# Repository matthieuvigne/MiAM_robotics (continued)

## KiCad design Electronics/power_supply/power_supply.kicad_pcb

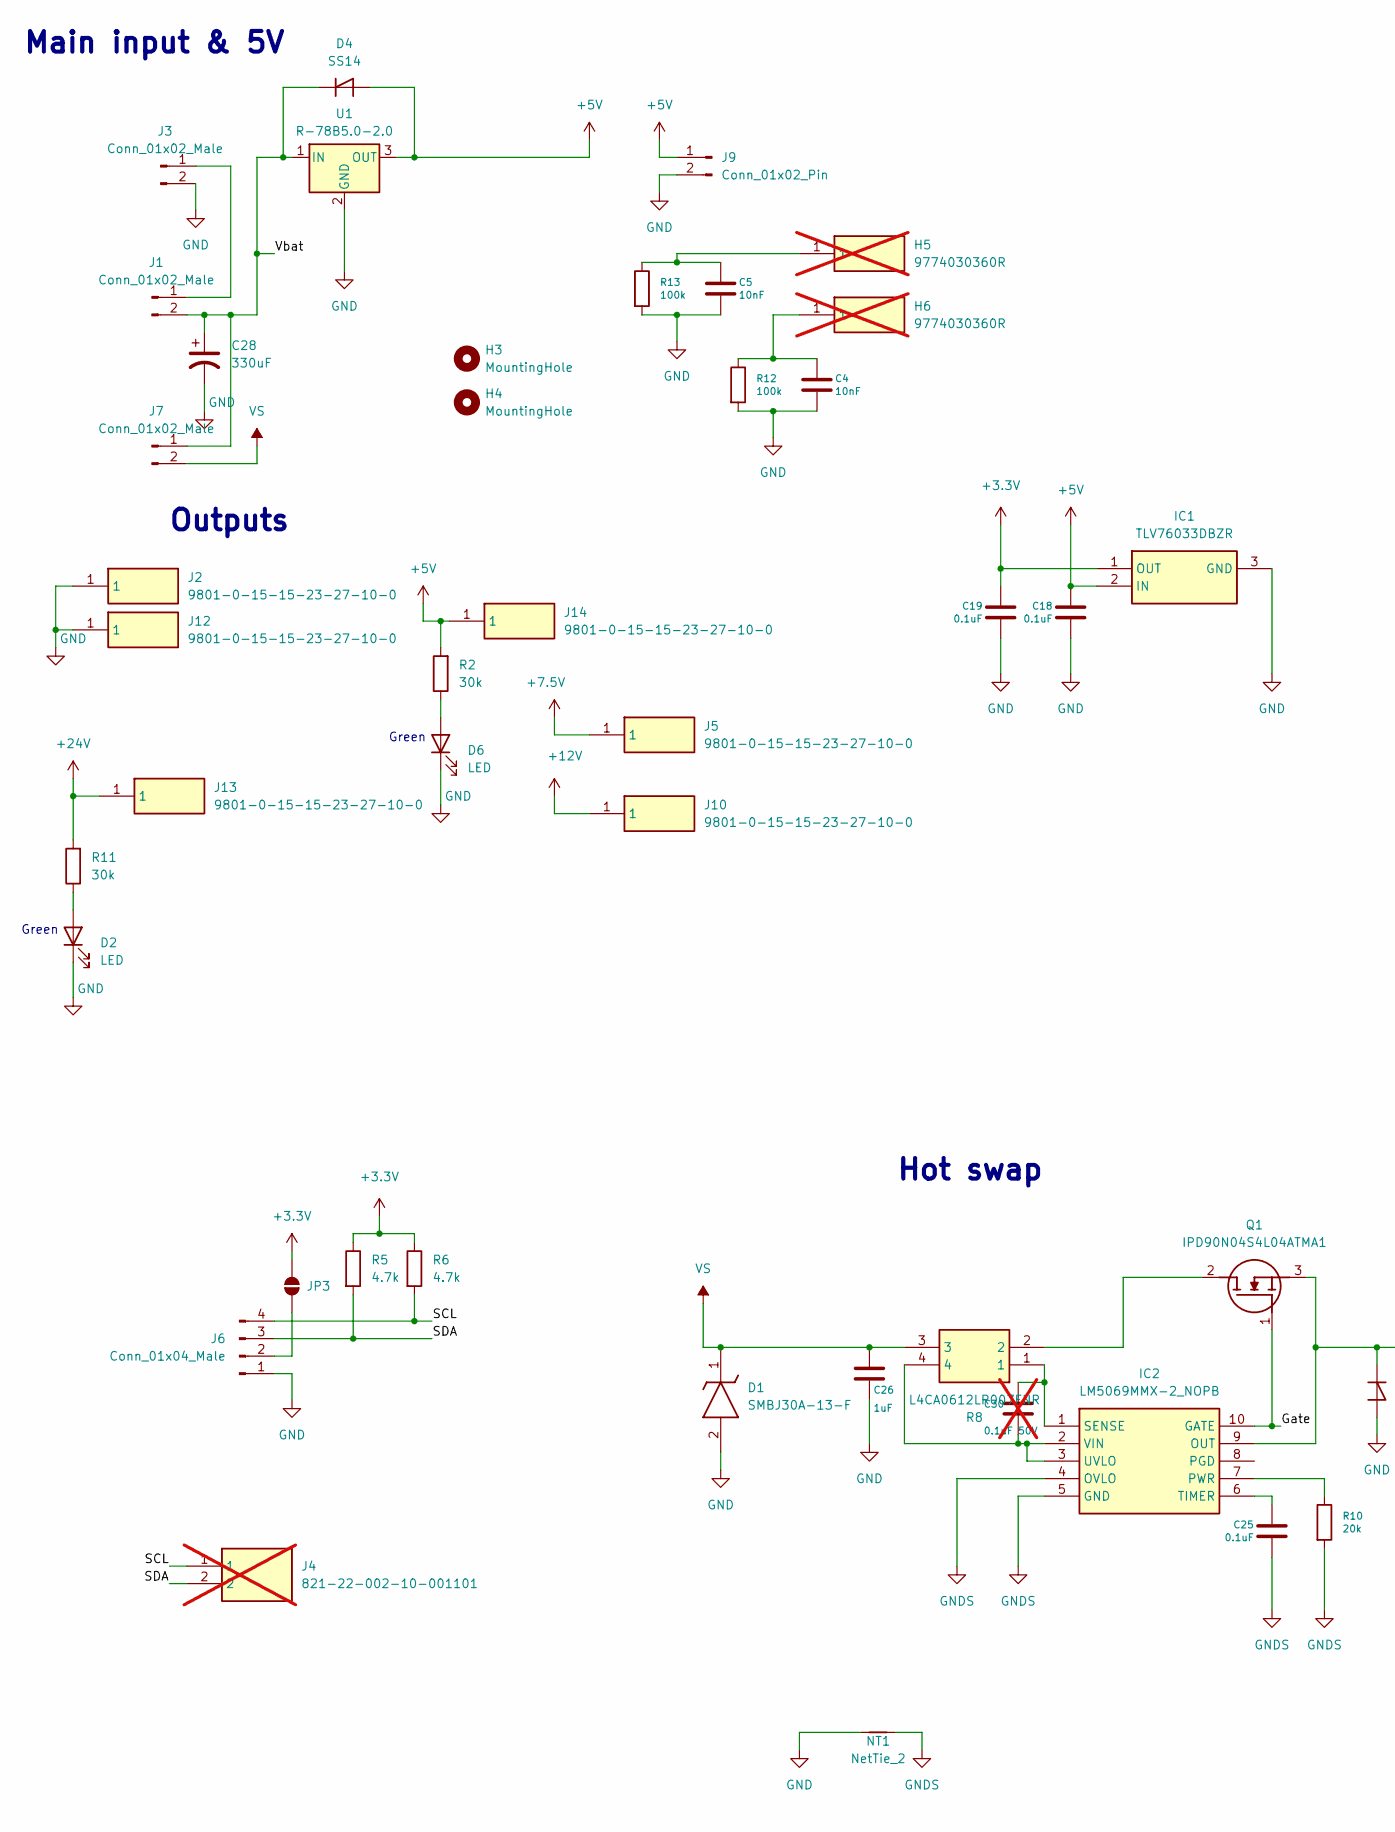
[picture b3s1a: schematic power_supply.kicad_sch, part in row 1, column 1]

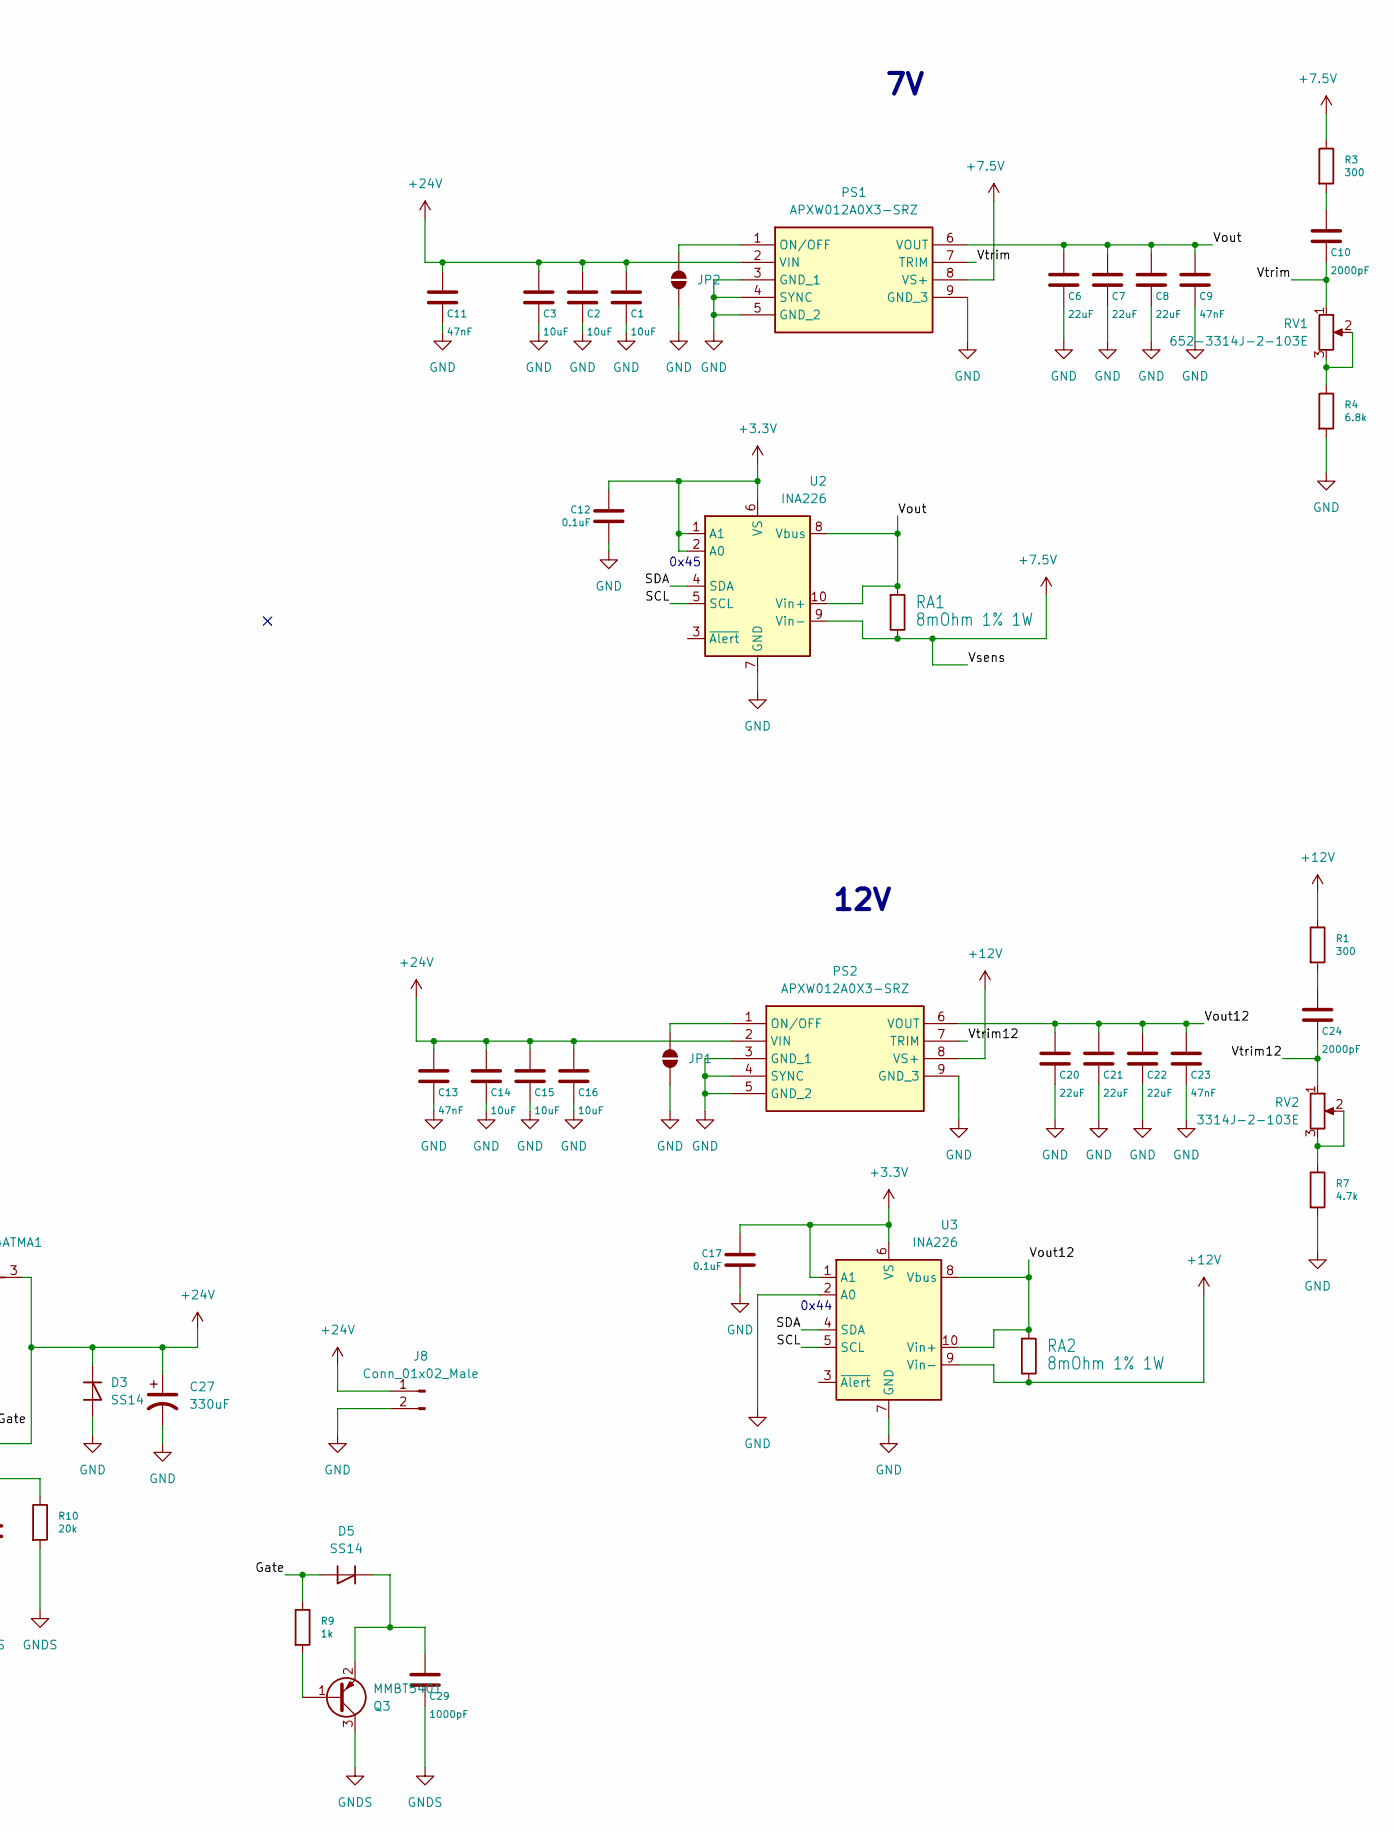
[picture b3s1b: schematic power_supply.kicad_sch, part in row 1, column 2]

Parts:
C1, C2, C3, C14, C15, C16: 10uF; C_1206_3216Metric_Pad1.33x1.80mm_HandSolder; MPN CL31A106MBHNNNE; Mouser Part Number 187-CL31A106MBHNNNE
C4, C5: 10nF; C_0805_2012Metric
C6, C7, C8, C20, C21, C22: 22uF; C_1206_3216Metric_Pad1.33x1.80mm_HandSolder; MPN CL31A226MOCLNNC; Mouser Part Number 187-CL31A226MOCLNNC
C9, C11, C13, C23: 47nF; C_0805_2012Metric_Pad1.18x1.45mm_HandSolder; MPN 0805YC473KAT2A; Mouser Part Number 581-0805YC473K
C10, C24: 2000pF; C_0805_2012Metric_Pad1.18x1.45mm_HandSolder; MPN CL21B202KBANNNC; Mouser Part Number 187-CL21B202KBANNNC
C12, C17, C19, C25: 0.1uF; C_0805_2012Metric
C18: 0.1uF; C_0805_2012Metric; MPN MF-CAP-0402-0.1uF
C26: 1uF; C_0805_2012Metric_Pad1.18x1.45mm_HandSolder; Mouser Part Number 187-CL21B105MBFNNNE
C27, C28: 330uF; CP_Radial_D10.0mm_P5.00mm; Mouser ECA-1VM331B
C29: 1000pF; C_0805_2012Metric_Pad1.18x1.45mm_HandSolder; Mouser Part Number 581-08055C102KAT4A
C30: 0.1uF 50V; C_0402_1005Metric_Pad0.74x0.62mm_HandSolder; MPN CGA2B3X7R1H104K050BB; not fitted
D1: SMBJ30A-13-F; DIOM5336X250N; Manufacturer_Part_Number SMBJ30A-13-F; Mouser 621-SMBJ30A-13-F
D2, D6: LED; LED_0805_2012Metric_Pad1.15x1.40mm_HandSolder
D3, D4, D5: SS14; DIONM5327X242N
H3, H4: MountingHole; MountingHole_3.2mm_M3
H5, H6: 9774030360R; Manufacturer_Part_Number 9774030360R; Mouser Part Number 710-9774030360R; not fitted
IC1: TLV76033DBZR; SOT95P237X112-3N; Manufacturer_Part_Number TLV76033DBZR; Mouser Part Number 595-TLV76033DBZR
IC2: LM5069MMX-2_NOPB; SOP50P490X110-10N; Manufacturer_Part_Number LM5069MMX-2/NOPB; Mouser Part Number 926-LM5069MMX-2/NOPB
J1, J3, J7, J8: Conn_01x02_Male; XT30UM
J2, J5, J10, J12, J13, J14: 9801-0-15-15-23-27-10-0; 9801015152327100; Manufacturer_Part_Number 9801-0-15-15-23-27-10-0; Mouser Part Number 575-9801015152327
J4: 821-22-002-10-001101; 8212200210000101; Manufacturer_Part_Number 821-22-002-10-000101; Mouser Part Number 575-8212200210001101; not fitted
J6: Conn_01x04_Male; JST_SH_SM04B-SRSS-TB_1x04-1MP_P1.00mm_Horizontal
J9: Conn_01x02_Pin; PinHeader_1x02_P2.54mm_Vertical
JP1, JP2, JP3: SolderJumper_2_Open; SolderJumper-2_P1.3mm_Open_RoundedPad1.0x1.5mm
NT1: NetTie_2; NetTie-2_SMD_Pad0.5mm
PS1: APXW012A0X3-SRZ; APXW012A0X3SRDZ_TH; Manufacturer_Part_Number APXW012A0X3-SRDZ; Mouser Part Number 894-APXW012A0X3-SRDZ
PS2: APXW012A0X3-SRZ; APXW012A0X3SRDZ_TH; Manufacturer_Part_Number APXW012A0X3-SRDZ; Mouser Part Number 894-APXW005A0X3-SRZ
Q1: IPD90N04S4L04ATMA1; Manufacturer_Part_Number IPD90N04S4L04ATMA1; Mouser Part Number 726-IPD90N04S4L04ATM
Q3: MMBT5401; SOT-23; Mouser 165-8634
R1, R3: 300; R_0805_2012Metric_Pad1.20x1.40mm_HandSolder; MPN RC0402FR-0710KL
R2, R11: 30k; R_0805_2012Metric
R4: 6.8k; R_0805_2012Metric_Pad1.20x1.40mm_HandSolder; MPN RC0402FR-0710KL
R5, R6: 4.7k; R_0805_2012Metric_Pad1.20x1.40mm_HandSolder
R7: 4.7k; R_0805_2012Metric_Pad1.20x1.40mm_HandSolder; MPN RC0402FR-0710KL
R8: L4CA0612LR007FNR; L4CA0612L0M50FNR; Manufacturer_Part_Number L4CA0612LR007FNR; Mouser Part Number 576-L4CA0612LR007FNR
R9: 1k; R_0805_2012Metric_Pad1.20x1.40mm_HandSolder; MPN RC0402FR-0710KL
R10: 20k; R_0805_2012Metric_Pad1.20x1.40mm_HandSolder
R12, R13: 100k; R_0805_2012Metric
RA1, RA2: 8mOhm 1% 1W; R_1206_3216Metric_Pad1.30x1.75mm_HandSolder; Mouser Part Number 504-MSMA1206R0080FCM
RV1: 652-3314J-2-103E; Potentiometer_Bourns_3314J_Vertical; Mouser 652-3314J-2-103E
RV2: 3314J-2-103E; Potentiometer_Bourns_3314J_Vertical; Mouser 652-3314J-2-103E
U1: R-78B5.0-2.0; Converter_DCDC_RECOM_R-78B-2.0_THT; Mouser R-78B5.0-2.0
U2, U3: INA226; VSSOP-10_3x3mm_P0.5mm

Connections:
+3.3V: C12.1, C17.1, C19.1, IC1.1 (OUT), JP3.2 (B), R5.1, R6.1, U2.1 (A1), U2.2 (A0), U2.6 (VS), U3.1 (A1), U3.6 (VS)
+5V: C18.1, D4.2 (A), IC1.2 (IN), J9.1, J14.1, R2.2, U1.3 (OUT)
+7.5V: J5.1, PS1.8 (VS+), R3.1, RA1.1, U2.9 (Vin-)
+12V: J10.1, PS2.8 (VS+), R1.1, RA2.1, U3.9 (Vin-)
+24V: C1.1, C2.1, C3.1, C11.1, C13.1, C14.1, C15.1, C16.1, C27.1, D3.1 (K), IC2.9 (OUT), J8.1, J13.1, PS1.2 (VIN), PS2.2 (VIN), Q1.3 (S), R11.2
/Gate: D5.2 (A), IC2.10 (GATE), Q1.1 (G), R9.1
/SCL: J4.1, J6.4, R6.2, U2.5 (SCL), U3.5 (SCL)
/SDA: J4.2, J6.3, R5.2, U2.4 (SDA), U3.4 (SDA)
/Vbat: C28.1, D4.1 (K), J1.2, J7.1, U1.1 (IN)
/Vout: C6.1, C7.1, C8.1, C9.1, PS1.6 (VOUT), RA1.2, U2.8 (Vbus), U2.10 (Vin+)
/Vout12: C20.1, C21.1, C22.1, C23.1, PS2.6 (VOUT), RA2.2, U3.8 (Vbus), U3.10 (Vin+)
/Vtrim: C10.2, PS1.7 (TRIM), RV1.1
/Vtrim12: C24.2, PS2.7 (TRIM), RV2.1
GND: C1.2, C2.2, C3.2, C4.2, C5.2, C6.2, C7.2, C8.2, C9.2, C11.2, C12.2, C13.2, C14.2, C15.2, C16.2, C17.2, C18.2, C19.2, C20.2, C21.2, C22.2, C23.2, C26.2, C27.2, C28.2, D1.2 (A), D2.1 (K), D3.2 (A), D6.1 (K), IC1.3 (GND), J2.1, J3.2, J6.1, J8.2, J9.2, J12.1, JP1.1 (A), JP2.1 (A), NT1.2, PS1.3 (GND_1), PS1.4 (SYNC), PS1.5 (GND_2), PS1.9 (GND_3), PS2.3 (GND_1), PS2.4 (SYNC), PS2.5 (GND_2), PS2.9 (GND_3), R4.2, R7.2, R12.2, R13.2, U1.2 (GND), U2.7 (GND), U3.2 (A0), U3.7 (GND)
GNDS: C25.2, C29.2, IC2.4 (OVLO), IC2.5 (GND), NT1.1, Q3.3 (C), R10.2
unnamed: C4.1, H6.1, R12.1
unnamed: C5.1, H5.1, R13.1
unnamed: C10.1, R3.2
unnamed: C24.1, R1.2
unnamed: D2.2 (A), R11.1
unnamed: C29.1, D5.1 (K), Q3.2 (E)
unnamed: D6.2 (A), R2.1
unnamed: IC2.7 (PWR), R10.1
unnamed: C30.1, IC2.1 (SENSE), R8.1
unnamed: C25.1, IC2.6 (TIMER)
unnamed: C30.2, IC2.2 (VIN), IC2.3 (UVLO), R8.4
unnamed: J1.1, J3.1
unnamed: J6.2, JP3.1 (A)
unnamed: JP1.2 (B), PS2.1 (ON/OFF)
unnamed: JP2.2 (B), PS1.1 (ON/OFF)
unnamed: Q1.2 (D), R8.2
unnamed: Q3.1 (B), R9.2
unnamed: R4.1, RV1.2, RV1.3
unnamed: R7.1, RV2.2, RV2.3
VS: C26.1, D1.1 (K), J7.2, R8.3

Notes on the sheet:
Green
Main input & 5V
0x44
12V
0x45
Outputs
Hot swap

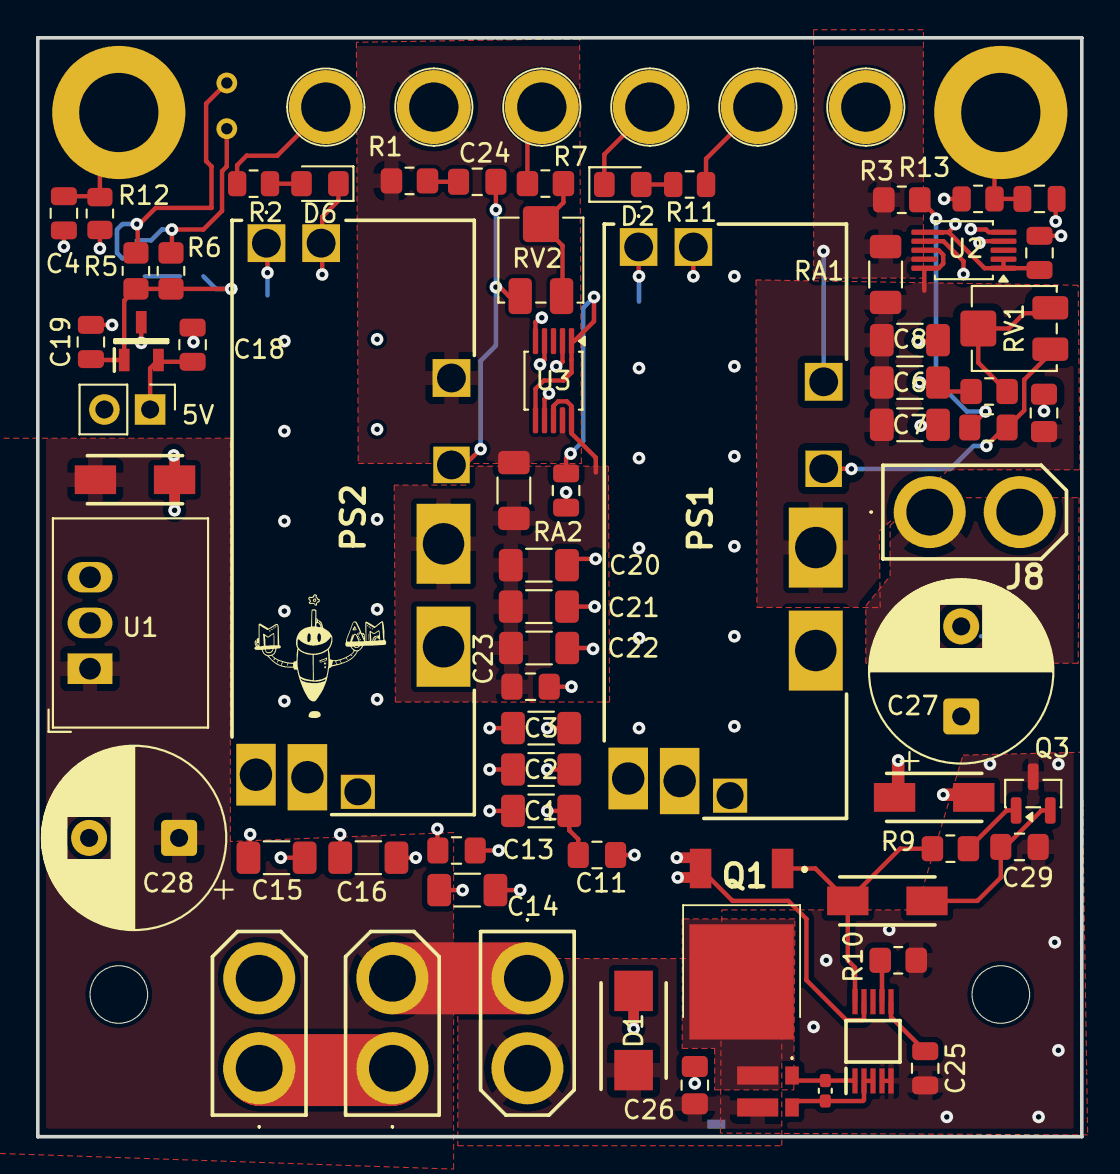
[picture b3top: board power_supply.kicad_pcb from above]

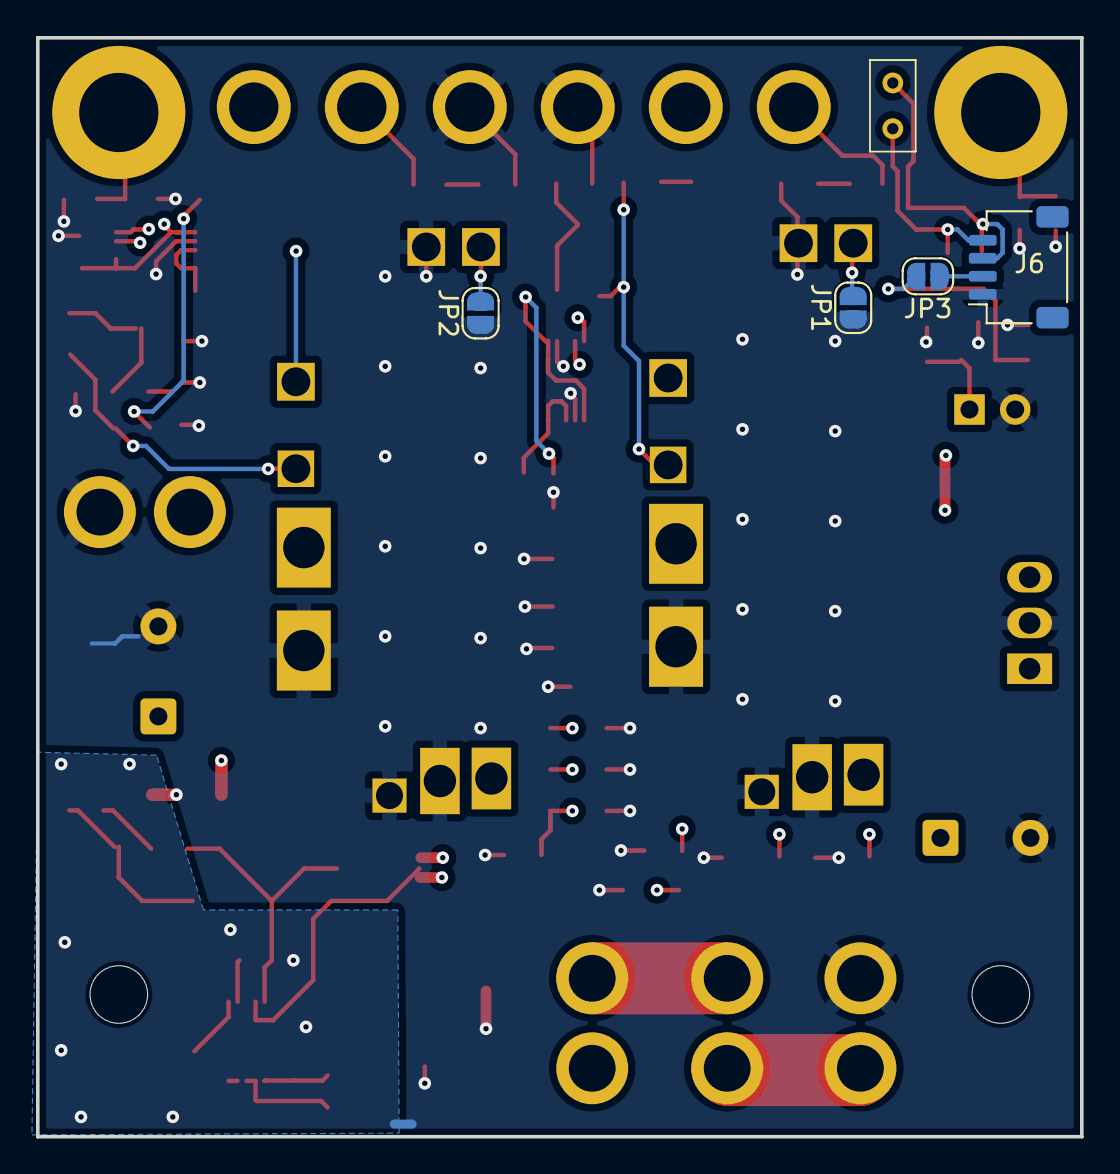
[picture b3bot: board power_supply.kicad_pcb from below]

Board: 4 copper layers, 58.0 x 61.0 mm, 83 parts (6 on the bottom side), 35 nets.

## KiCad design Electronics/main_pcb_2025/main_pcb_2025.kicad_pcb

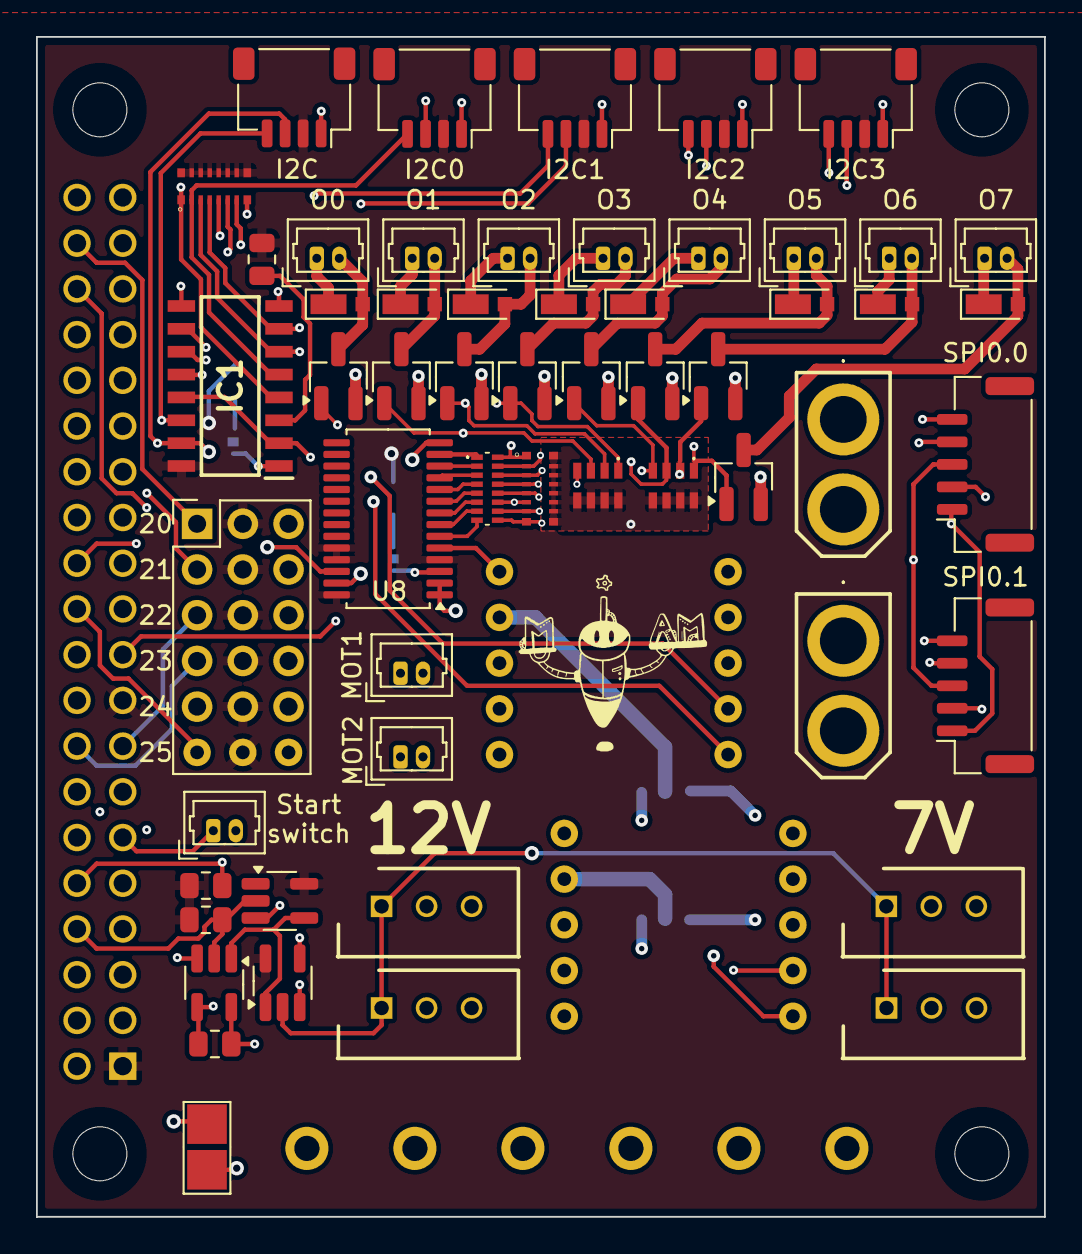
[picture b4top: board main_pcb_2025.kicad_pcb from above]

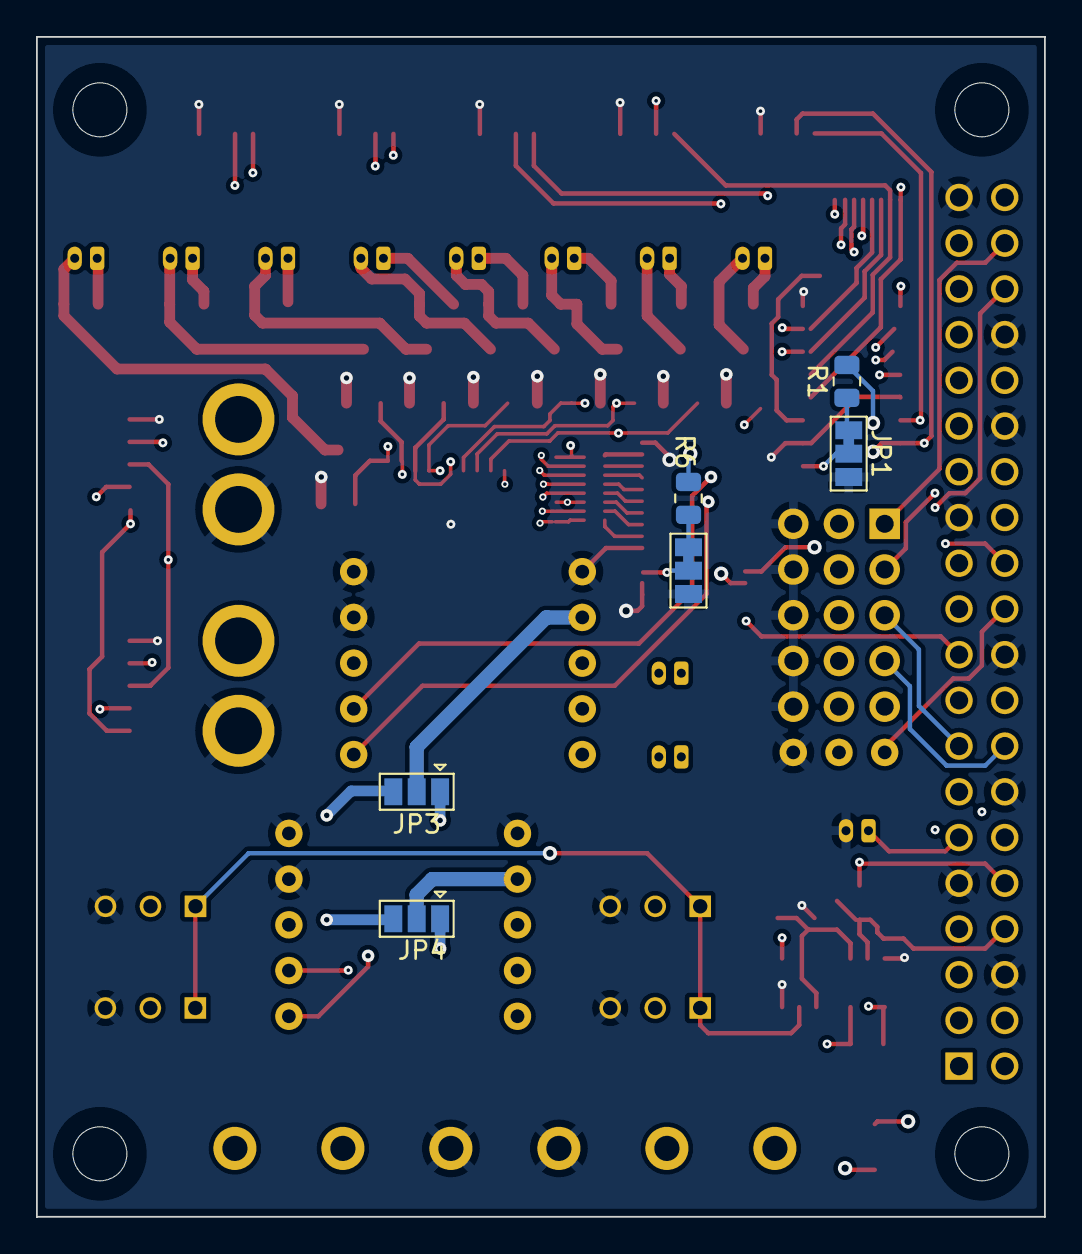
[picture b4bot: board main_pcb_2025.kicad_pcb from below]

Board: 4 copper layers, 56.0 x 65.5 mm, 71 parts (6 on the bottom side), 71 nets.

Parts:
C1, C2: W3A45A101KAT2A
C3: Conn_03x06; Pin_Header_Straight_3x06_Pitch2.54mm
D3, D4, D5, D6, D7, D8, D9, D10: MSS2P3; D_MicroSMP_AK
I2C0, I2C1, I2C2, I2C3, I2C4: Conn_01x04_Male; JST_SH_SM04B-SRSS-TB_1x04-1MP_P1.00mm_Horizontal
IC1: PCA9546AD; SOIC127P600X175-16N
J1: PI40HAT; MODULE_RASPBERRY_PI_B+
J2, J3, J4, J28, J29, J30: MilliMax0600; 0600005150000
J5, J6: Conn_01x02_Male; XT30UM
J9, J23, J31, J32: 22-03-5035; SHDR3W60P0X250_1X3_990X490X590P
J14: Conn_01x02_Pin; PogoPin_2.54
J24: Conn_01x02_Male; Molex_PicoBlade_53047-0210_1x02_P1.25mm_Vertical
JP1, JP2: SolderJumper_3_Bridged12; SolderJumper-3_P1.3mm_Bridged12_Pad1.0x1.5mm_NumberLabels
JP3, JP4: SolderJumper_3_Open; SolderJumper-3_P1.3mm_Open_Pad1.0x1.5mm
MOT1, MOT2: Conn_01x02_Male; Molex_PicoBlade_53047-0210_1x02_P1.25mm_Vertical
O0, O1, O2, O3, O4, O5, O6, O7: Conn_01x02_Male; Molex_PicoBlade_53047-0210_1x02_P1.25mm_Vertical
Q1, Q2, Q3, Q4, Q5, Q6, Q7, Q8: NVTR4503NT1G; SOT-23_Handsoldering
R1, R6, R12, R14: 10k; R_0805_2012Metric
R4: 2k; R_0805_2012Metric
R11: 4k; R_0805_2012Metric
RN1: EXB-2HV472JV; EXB2HV_1
RN2: YC248-JR-071KL; YC248JR0710KL
RN3: EXB-2HV473JV; EXB2HV_1
SPI0, SPI2: JST_ZH5; JST_GH_SM05B-GHS-TB_1x05-1MP_P1.25mm_Horizontal
U1: SN74LVC1G125DBVR; SOT-23-5_HandSoldering
U2: SN74LVC1G04DBVR; SOT-23-5_HandSoldering
U4, U6: Pololu_MAX14870; PololuMAX14870
U7: SN74AHCT1G126DBVR; SOT-23-5_HandSoldering
U8: PCA9635; TSSOP-28_4.4x9.7mm_P0.65mm

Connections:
+3.3V: C3.2, C3.5, C3.8, C3.11, C3.14, C3.17, I2C0.2, I2C1.2, I2C2.2, I2C3.2, I2C4.2, IC1.16 (VCC), J1.1 (P3V3), J1.17 (P3V3), R1.2, R6.2, R11.2, R12.2, R14.2, RN1.9, RN1.10, RN1.11, RN1.12, RN1.13, RN1.14, RN1.15, RN1.16, U1.5 (VCC), U2.5 (VCC), U8.4 (A3), U8.24 (A5), U8.25 (A6), U8.28 (VDD)
+5V: J1.2 (P5V), J1.4 (P5V), J4.1, R4.2, U7.5 (VCC)
+7.5V: J2.1, J9.2, J23.2, JP3.3 (B), JP4.3 (B)
+12V: J3.1, J31.2, J32.2
+24V: D3.1 (K), D4.1 (K), D5.1 (K), D6.1 (K), D7.1 (K), D8.1 (K), D9.1 (K), D10.1 (K), J5.1, J6.1, J30.1, JP3.1 (A), JP4.1 (A), O0.1, O1.1, O2.1, O3.1, O4.1, O5.1, O6.1, O7.1
/A0: IC1.1 (A0), JP1.2 (C)
/A2: JP2.2 (C), U8.3 (A2)
/GPIO 12: J1.32 (BCM12), U4.1 (PWM)
/GPIO 13: J1.33 (BCM13), U6.1 (PWM)
/GPIO 16: J1.36 (BCM16), U4.2 (DIR)
/GPIO 17: J1.11 (BCM17), J24.1
/GPIO 19: J1.35 (BCM19), U6.2 (DIR)
/GPIO 20: C3.1, J1.38 (BCM20)
/GPIO 21: C3.4, J1.40 (BCM21)
/GPIO 22: C3.7, J1.15 (BCM22)
/GPIO 23: C3.10, J1.16 (BCM23)
/GPIO 24: C3.13, J1.18 (BCM24)
/GPIO 25: C3.16, J1.22 (BCM25)
/I2C SCL: I2C4.4, IC1.14 (SCL), J1.5 (BCM3), J14.1, U8.26 (SCL)
/I2C SDA: I2C4.3, IC1.15 (SDA), J1.3 (BCM2), J14.2, U8.27 (SDA)
/S0: C1.4, Q1.1 (G), RN2.16, RN3.8
/S1: C1.3, Q2.1 (G), RN2.14, RN3.7
/S2: C1.2, Q3.1 (G), RN2.12, RN3.6
/S3: C1.1, Q4.1 (G), RN2.10, RN3.5
/S4: C2.4, Q5.1 (G), RN2.8, RN3.4
/S5: C2.3, Q6.1 (G), RN2.6, RN3.3
/S6: C2.2, Q7.1 (G), RN2.4, RN3.2
/S7: C2.1, Q8.1 (G), RN2.2, RN3.1
/SCL0: I2C0.4, IC1.5 (SC0), RN1.2
/SCL1: I2C1.4, IC1.7 (SC1), RN1.4
/SCL2: I2C2.4, IC1.10 (SC2), RN1.6
/SCL3: I2C3.4, IC1.12 (SC3), RN1.8
/SDA0: I2C0.3, IC1.4 (SD0), RN1.1
/SDA1: I2C1.3, IC1.6 (SD1), RN1.3
/SDA2: I2C2.3, IC1.9 (SD2), RN1.5
/SDA3: I2C3.3, IC1.11 (SD3), RN1.7
/SPI0 CLK: J1.23 (BCM11), SPI0.1, SPI2.1
/SPI0 MISO: J1.21 (BCM9), SPI0.2, SPI2.2
/SPI0 MOSI: J1.19 (BCM10), SPI0.3, SPI2.3
/SPI0_CS0: J1.24 (BCM8), SPI0.4
/SPI0_CS1: J1.26 (BCM7), SPI2.4
/TX_EN: U1.1, U2.4, U7.1
/UART_HalfDuplex: J9.1, J23.1, J31.1, J32.1, R4.1, U1.2, U7.4
/UART_RX: J1.10 (BCM15), R12.1, U1.4
/UART_TX: J1.8 (BCM14), R14.1, U2.2, U7.2
GND: C1.5, C1.6, C1.7, C1.8, C2.5, C2.6, C2.7, C2.8, C3.3, C3.6, C3.9, C3.12, C3.15, C3.18, I2C0.1, I2C1.1, I2C2.1, I2C3.1, I2C4.1, IC1.2 (A1), IC1.8 (GND), IC1.13 (A2), J1.6 (GND), J1.9 (GND), J1.14 (GND), J1.20 (GND), J1.25 (GND), J1.30 (GND), J1.34 (GND), J1.39 (GND), J5.2, J6.2, J9.3, J23.3, J24.2, J28.1, J29.1, J31.3, J32.3, JP1.3 (B), JP2.3 (B), Q1.2 (S), Q2.2 (S), Q3.2 (S), Q4.2 (S), Q5.2 (S), Q6.2 (S), Q7.2 (S), Q8.2 (S), RN3.9, RN3.10, RN3.11, RN3.12, RN3.13, RN3.14, RN3.15, RN3.16, SPI0.5, SPI2.5, U1.3 (GND), U2.3 (GND), U4.4 (nEnable), U4.5 (GND), U6.4 (nEnable), U6.5 (GND), U7.3 (GND), U8.1 (A0), U8.2 (A1), U8.5 (A4), U8.14 (VSS)
unnamed: D3.2 (A), O0.2, Q1.3 (D)
unnamed: D4.2 (A), O1.2, Q2.3 (D)
unnamed: D5.2 (A), O2.2, Q3.3 (D)
unnamed: D6.2 (A), O3.2, Q4.3 (D)
unnamed: D7.2 (A), O4.2, Q5.3 (D)
unnamed: D8.2 (A), O5.2, Q6.3 (D)
unnamed: D9.2 (A), O6.2, Q7.3 (D)
unnamed: D10.2 (A), O7.2, Q8.3 (D)
unnamed: IC1.3 (~RESET), R11.1
unnamed: JP1.1 (A), R1.1
unnamed: JP2.1 (A), R6.1
unnamed: JP3.2 (C), U6.9 (Vin)
unnamed: JP4.2 (C), U4.9 (Vin)
unnamed: MOT1.1, U6.7 (M1)
unnamed: MOT1.2, U6.8 (M2)
unnamed: MOT2.1, U4.7 (M1)
unnamed: MOT2.2, U4.8 (M2)
unnamed: RN2.15, U8.6 (LED0)
unnamed: RN2.13, U8.7 (LED1)
unnamed: RN2.11, U8.8 (LED2)
unnamed: RN2.9, U8.9 (LED3)
unnamed: RN2.7, U8.10 (LED4)
unnamed: RN2.5, U8.11 (LED5)
unnamed: RN2.3, U8.12 (LED6)
unnamed: RN2.1, U8.13 (LED7)

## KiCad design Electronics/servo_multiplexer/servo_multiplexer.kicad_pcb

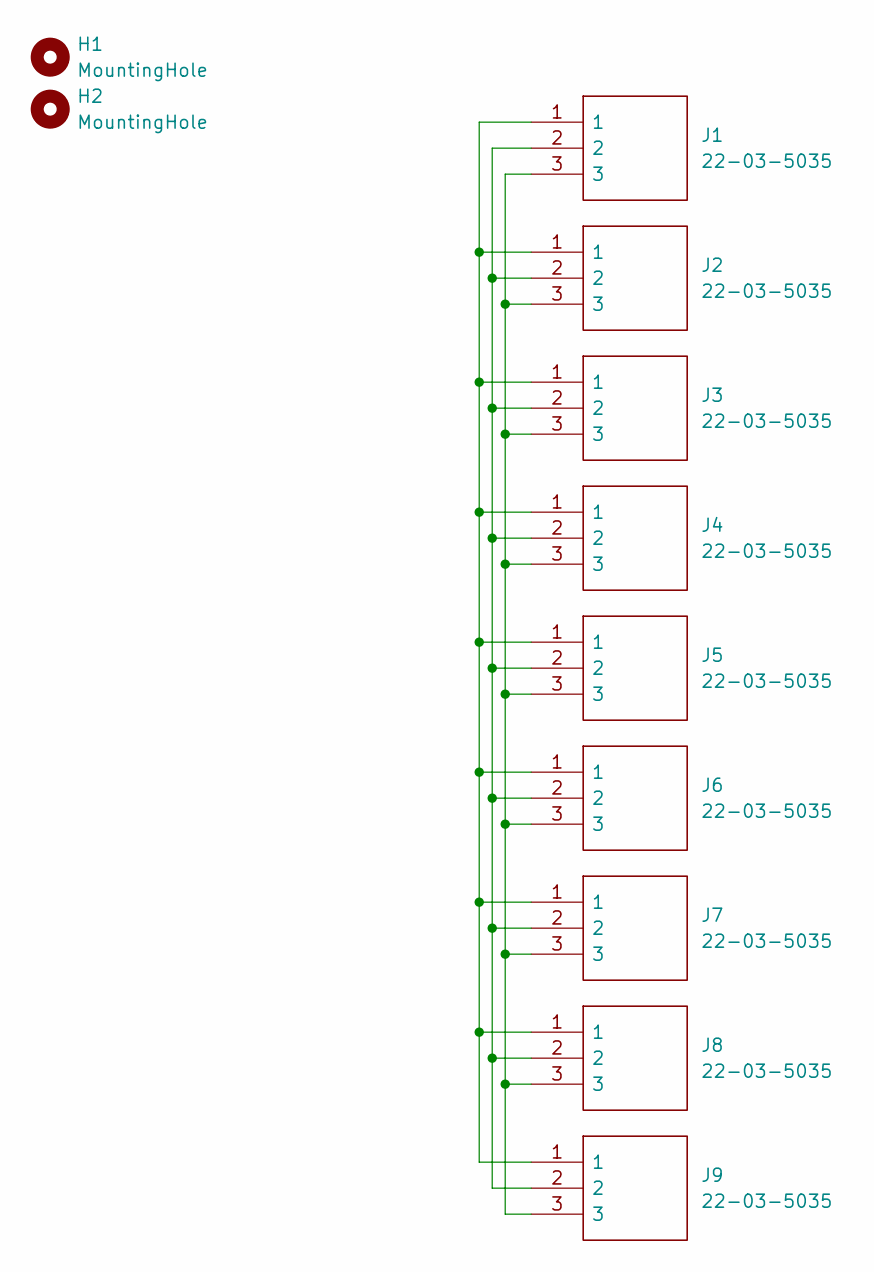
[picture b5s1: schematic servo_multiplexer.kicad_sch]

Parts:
H1, H2: MountingHole; MountingHole_3.2mm_M3
J1, J2, J3, J4, J5, J6, J7, J8, J9: 22-03-5035; SHDR3W60P0X250_1X3_990X490X590P; Manufacturer_Part_Number 22-03-5035

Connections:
unnamed: J1.1, J2.1, J3.1, J4.1, J5.1, J6.1, J7.1, J8.1, J9.1
unnamed: J1.2, J2.2, J3.2, J4.2, J5.2, J6.2, J7.2, J8.2, J9.2
unnamed: J1.3, J2.3, J3.3, J4.3, J5.3, J6.3, J7.3, J8.3, J9.3

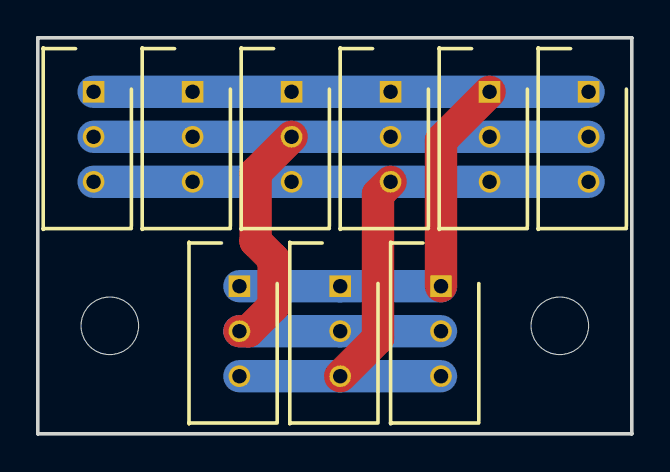
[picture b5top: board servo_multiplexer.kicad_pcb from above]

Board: 2 copper layers, 33.0 x 22.0 mm, 11 parts (0 on the bottom side), 3 nets.

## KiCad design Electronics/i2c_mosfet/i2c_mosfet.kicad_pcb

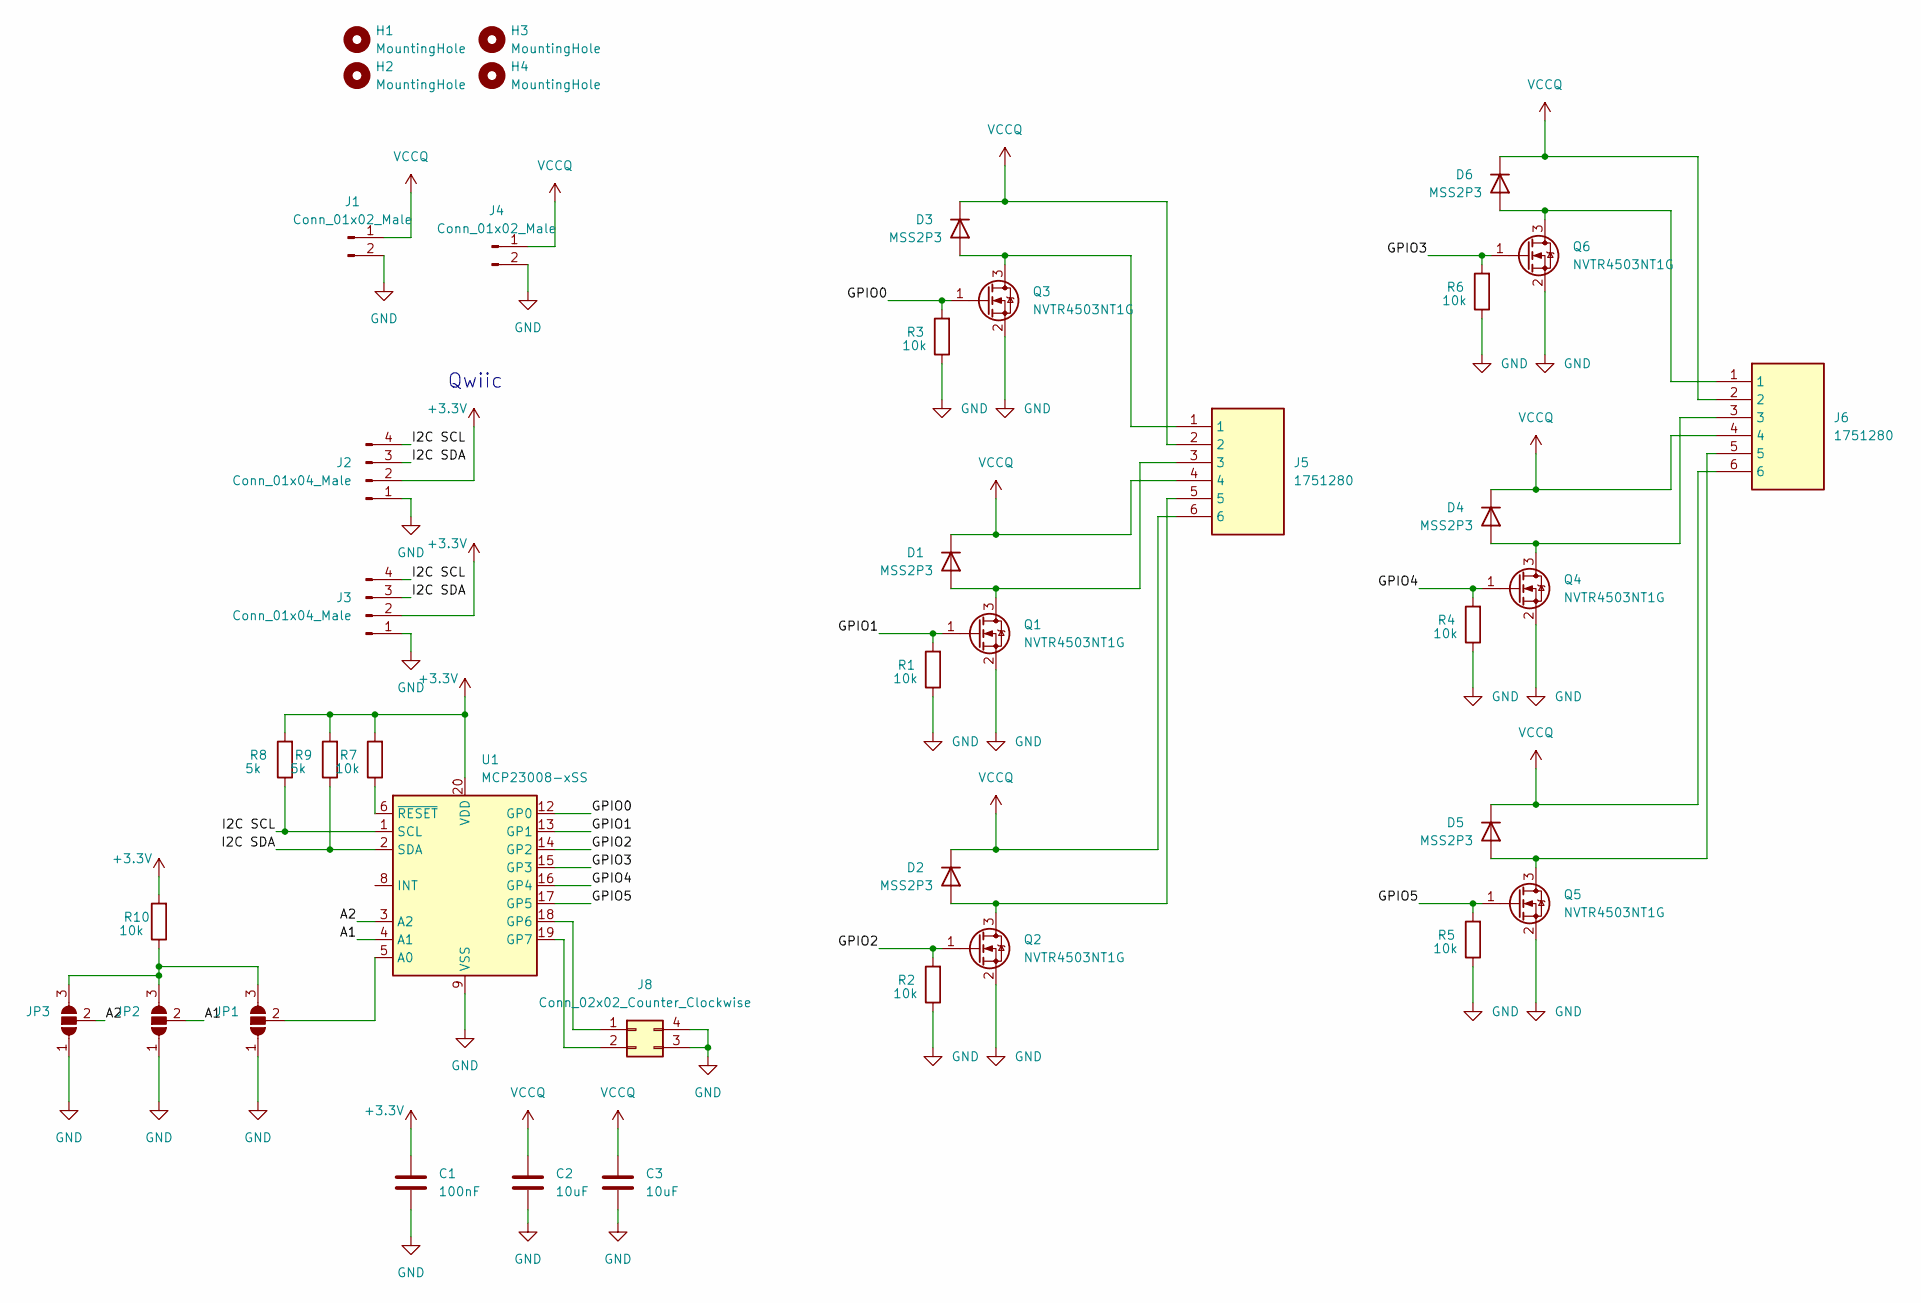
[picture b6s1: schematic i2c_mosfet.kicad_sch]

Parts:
C1: 100nF; C_0402_1005Metric_Pad0.74x0.62mm_HandSolder
C2, C3: 10uF; C_1206_3216Metric_Pad1.33x1.80mm_HandSolder
D1, D2, D3, D4, D5, D6: MSS2P3; D_MicroSMP_AK
H1, H2, H3, H4: MountingHole; MountingHole_3.2mm_M3
J1, J4: Conn_01x02_Male; XT30UM
J2, J3: Conn_01x04_Male; JST_SH_SM04B-SRSS-TB_1x04-1MP_P1.00mm_Horizontal
J5, J6: 1751280
J8: Conn_02x02_Counter_Clockwise; PinHeader_2x02_P2.54mm_Vertical
JP1, JP2, JP3: SolderJumper_3_Open; SolderJumper-3_P1.3mm_Open_Pad1.0x1.5mm
Q1, Q2, Q3, Q4, Q5, Q6: NVTR4503NT1G; SOT-23_Handsoldering
R1, R2, R3, R4, R5, R6, R7, R10: 10k; R_0805_2012Metric
R8, R9: 5k; R_0805_2012Metric
U1: MCP23008-xSS; SSOP-20_5.3x7.2mm_P0.65mm

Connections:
+3.3V: C1.1, J2.2, J3.2, R7.2, R8.2, R9.2, R10.2, U1.20 (VDD)
/A1: JP2.2 (C), U1.4 (A1)
/A2: JP3.2 (C), U1.3 (A2)
/GPIO0: Q3.1 (G), R3.2, U1.12 (GP0)
/GPIO1: Q1.1 (G), R1.2, U1.13 (GP1)
/GPIO2: Q2.1 (G), R2.2, U1.14 (GP2)
/GPIO3: Q6.1 (G), R6.2, U1.15 (GP3)
/GPIO4: Q4.1 (G), R4.2, U1.16 (GP4)
/GPIO5: Q5.1 (G), R5.2, U1.17 (GP5)
/I2C SCL: J2.4, J3.4, R8.1, U1.1 (SCL)
/I2C SDA: J2.3, J3.3, R9.1, U1.2 (SDA)
GND: C1.2, C2.2, C3.2, J1.2, J2.1, J3.1, J4.2, J8.3, J8.4, JP1.1 (A), JP2.1 (A), JP3.1 (A), Q1.2 (S), Q2.2 (S), Q3.2 (S), Q4.2 (S), Q5.2 (S), Q6.2 (S), R1.1, R2.1, R3.1, R4.1, R5.1, R6.1, U1.9 (VSS)
unnamed: D1.2 (A), J5.3, Q1.3 (D)
unnamed: D2.2 (A), J5.5, Q2.3 (D)
unnamed: D3.2 (A), J5.1, Q3.3 (D)
unnamed: D4.2 (A), J6.3, Q4.3 (D)
unnamed: D5.2 (A), J6.5, Q5.3 (D)
unnamed: D6.2 (A), J6.1, Q6.3 (D)
unnamed: J8.1, U1.18 (GP6)
unnamed: J8.2, U1.19 (GP7)
unnamed: JP1.3 (B), JP2.3 (B), JP3.3 (B), R10.1
unnamed: JP1.2 (C), U1.5 (A0)
unnamed: R7.1, U1.6 (~RESET)
VCCQ: C2.1, C3.1, D1.1 (K), D2.1 (K), D3.1 (K), D4.1 (K), D5.1 (K), D6.1 (K), J1.1, J4.1, J5.2, J5.4, J5.6, J6.2, J6.4, J6.6

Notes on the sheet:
Qwiic

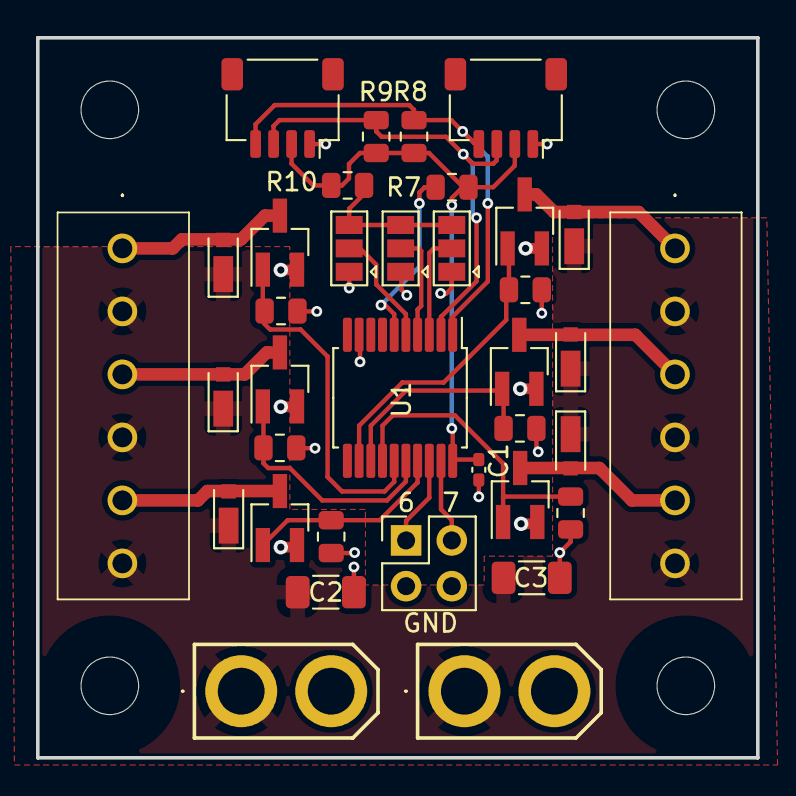
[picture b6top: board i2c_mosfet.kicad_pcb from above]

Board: 2 copper layers, 40.0 x 40.0 mm, 40 parts (0 on the bottom side), 24 nets.
